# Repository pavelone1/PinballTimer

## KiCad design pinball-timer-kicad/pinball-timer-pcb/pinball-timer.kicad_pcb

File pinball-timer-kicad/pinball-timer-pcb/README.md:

# Pinball 4-Player Timer — Carrier PCB (rev A)

KiCad 8 project. 160 x 100 mm, 2-layer. Open `pinball-timer.kicad_pcb` in KiCad's
PCB editor (pcbnew). All footprints are placed and every pad is already assigned
to its net — the ratsnest (thin white lines) shows you exactly what to route.

## What's on the board

| Ref  | Part                          | Nets on pins                        |
|------|-------------------------------|-------------------------------------|
| J1   | JST-XH 4-pin, Display 1       | 1:+5V  2:GND  3:DISP1_CLK  4:DISP1_DIO |
| J2   | JST-XH 4-pin, Display 2       | 1:+5V  2:GND  3:DISP2_CLK  4:DISP2_DIO |
| J3   | JST-XH 4-pin, Display 3       | 1:+5V  2:GND  3:DISP3_CLK  4:DISP3_DIO |
| J4   | JST-XH 4-pin, Display 4       | 1:+5V  2:GND  3:DISP4_CLK  4:DISP4_DIO |
| J5   | JST-XH 2-pin, Player 1 button | 1:BTN_P1      2:GND                 |
| J6   | JST-XH 2-pin, Player 2 button | 1:BTN_P2      2:GND                 |
| J7   | JST-XH 2-pin, Player 3 button | 1:BTN_P3      2:GND                 |
| J8   | JST-XH 2-pin, Player 4 button | 1:BTN_P4      2:GND                 |
| J9   | JST-XH 2-pin, Action button   | 1:BTN_ACTION  2:GND                 |
| J10  | JST-XH 2-pin, Buzzer          | 1:BUZZER      2:GND                 |
| U1A/B| 2x 1x22 female headers (ESP32-S3 socket) | see GPIO map below       |
| H1-4 | M3 mounting holes             | —                                   |

## GPIO map (ESP32-S3 DevKitC-1 style pinout)

| Signal      | GPIO | Signal      | GPIO |
|-------------|------|-------------|------|
| BTN_P1      | 4    | DISP1_CLK   | 10   |
| BTN_P2      | 5    | DISP1_DIO   | 11   |
| BTN_P3      | 6    | DISP2_CLK   | 12   |
| BTN_P4      | 7    | DISP2_DIO   | 13   |
| BTN_ACTION  | 8    | DISP3_CLK   | 14   |
| BUZZER      | 9    | DISP3_DIO   | 15   |
|             |      | DISP4_CLK   | 16   |
|             |      | DISP4_DIO   | 17   |

Buttons use internal pull-ups (INPUT_PULLUP); pressed = LOW. No external
resistors on the board.

## VERIFY BEFORE ORDERING — do not skip

1. **Header row spacing.** U1A/U1B are placed 22.86 mm (0.9 in) apart, the
   common ESP32-S3 DevKitC-1 spacing. Clone boards vary. Measure YOUR Hosyond
   board center-to-center across the two pin rows and move U1B if needed
   (select footprint, press M, type exact coordinates).
2. **Pin order.** The net assignments assume the standard DevKitC-1 pinout
   (left row top-to-bottom: 3V3, 3V3, RST, 4, 5, 6, 7, 15, 16, 17, 18, 8, 3,
   46, 9, 10, 11, 12, 13, 14, 5V, GND). Check the silkscreen on your actual
   board pin-by-pin. If your board differs, re-assign pad nets in KiCad
   (edit pad -> net) — 5 minutes of checking vs. a scrapped board order.
3. **Display voltage.** Display VCC is routed to the module's 5V pin, which is
   fed by the battery shield through the module's USB port. TM1637 accepts
   3.3 V logic at 5 V supply — standard practice, no level shifter needed.

## Routing (30-60 min by hand, or minutes with autorouter)

1. Open the .kicad_pcb, confirm footprint positions.
2. Route GND and +5V first at 0.6 mm (Power netclass is preconfigured), or
   skip and pour a GND zone on B.Cu + a +5V zone section instead.
3. Route the 14 signal nets at 0.3 mm. There is enormous room; nothing is tight.
4. Run DRC (ladybug icon). Zero errors required.

Optional autorouting: File -> Export -> Specctra DSN, run Freerouting
(freerouting.org), import the .ses back.

## Export Gerbers for PCBWay

1. File -> Fabrication Outputs -> Gerbers.
   Layers: F.Cu, B.Cu, F.SilkS, B.SilkS, F.Mask, B.Mask, Edge.Cuts.
   Format defaults are already set in this project. Click Plot.
2. Same dialog -> Generate Drill Files (Excellon, PTH+NPTH merged is fine).
3. Zip the gerbers/ folder, upload to pcbway.com instant quote.
   Board settings: 2 layers, 160 x 100 mm, 1.6 mm FR4, HASL, 5 pcs.

## Mating connector shopping (for the wire harness)

- JST-XH 2.54... (2.5 mm) housing + crimp terminal kits are sold as assortments;
  get a kit with 2-pin and 4-pin housings and pre-crimped wires if you don't
  own a crimper.

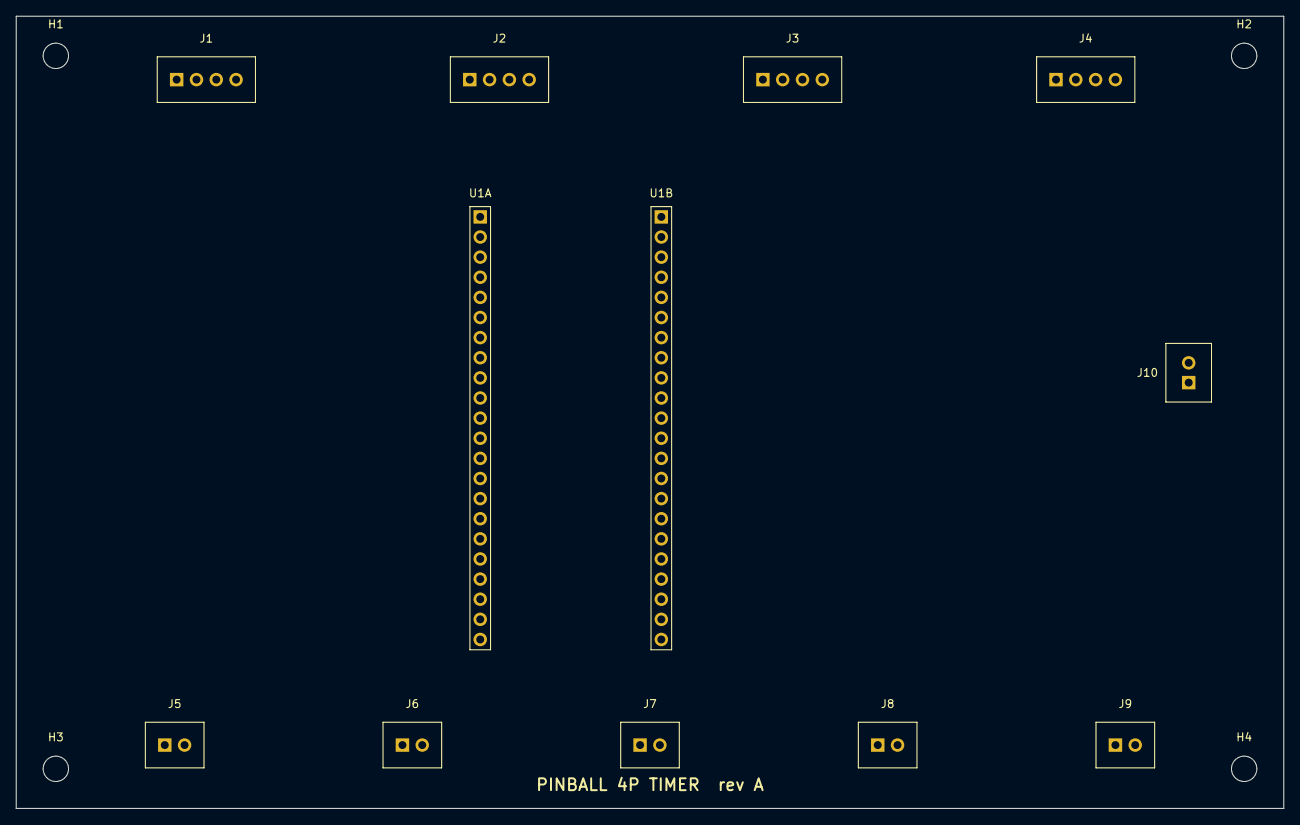
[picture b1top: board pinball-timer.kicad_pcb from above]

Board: 2 copper layers, 160.0 x 100.0 mm, 16 parts (0 on the bottom side), 16 nets, no tracks yet.

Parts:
H1, H2, H3, H4: M3; MountingHole_3.2mm_M3
J1: DISPLAY_1; JST_XH_B4B-XH-A_1x04_P2.50mm_Vertical
J2: DISPLAY_2; JST_XH_B4B-XH-A_1x04_P2.50mm_Vertical
J3: DISPLAY_3; JST_XH_B4B-XH-A_1x04_P2.50mm_Vertical
J4: DISPLAY_4; JST_XH_B4B-XH-A_1x04_P2.50mm_Vertical
J5: PLAYER_1; JST_XH_B2B-XH-A_1x02_P2.50mm_Vertical
J6: PLAYER_2; JST_XH_B2B-XH-A_1x02_P2.50mm_Vertical
J7: PLAYER_3; JST_XH_B2B-XH-A_1x02_P2.50mm_Vertical
J8: PLAYER_4; JST_XH_B2B-XH-A_1x02_P2.50mm_Vertical
J9: ACTION; JST_XH_B2B-XH-A_1x02_P2.50mm_Vertical
J10: BUZZER; JST_XH_B2B-XH-A_1x02_P2.50mm_Vertical
U1A: ESP32-S3_LEFT; PinSocket_1x22_P2.54mm_Vertical
U1B: ESP32-S3_RIGHT; PinSocket_1x22_P2.54mm_Vertical

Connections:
+5V: J1.1, J2.1, J3.1, J4.1, U1A.21
BTN_ACTION: J9.1, U1A.12
BTN_P1: J5.1, U1A.4
BTN_P2: J6.1, U1A.5
BTN_P3: J7.1, U1A.6
BTN_P4: J8.1, U1A.7
BUZZER: J10.1, U1A.15
DISP1_CLK: J1.3, U1A.16
DISP1_DIO: J1.4, U1A.17
DISP2_CLK: J2.3, U1A.18
DISP2_DIO: J2.4, U1A.19
DISP3_CLK: J3.3, U1A.20
DISP3_DIO: J3.4, U1A.8
DISP4_CLK: J4.3, U1A.9
DISP4_DIO: J4.4, U1A.10
GND: J1.2, J2.2, J3.2, J4.2, J5.2, J6.2, J7.2, J8.2, J9.2, J10.2, U1A.22, U1B.1, U1B.21, U1B.22
